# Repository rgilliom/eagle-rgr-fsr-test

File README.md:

# eagle-rgr-fsr-test
Ruger FSR Test Board for logging values using the 2-wire trigger circuit.  Eagle Project

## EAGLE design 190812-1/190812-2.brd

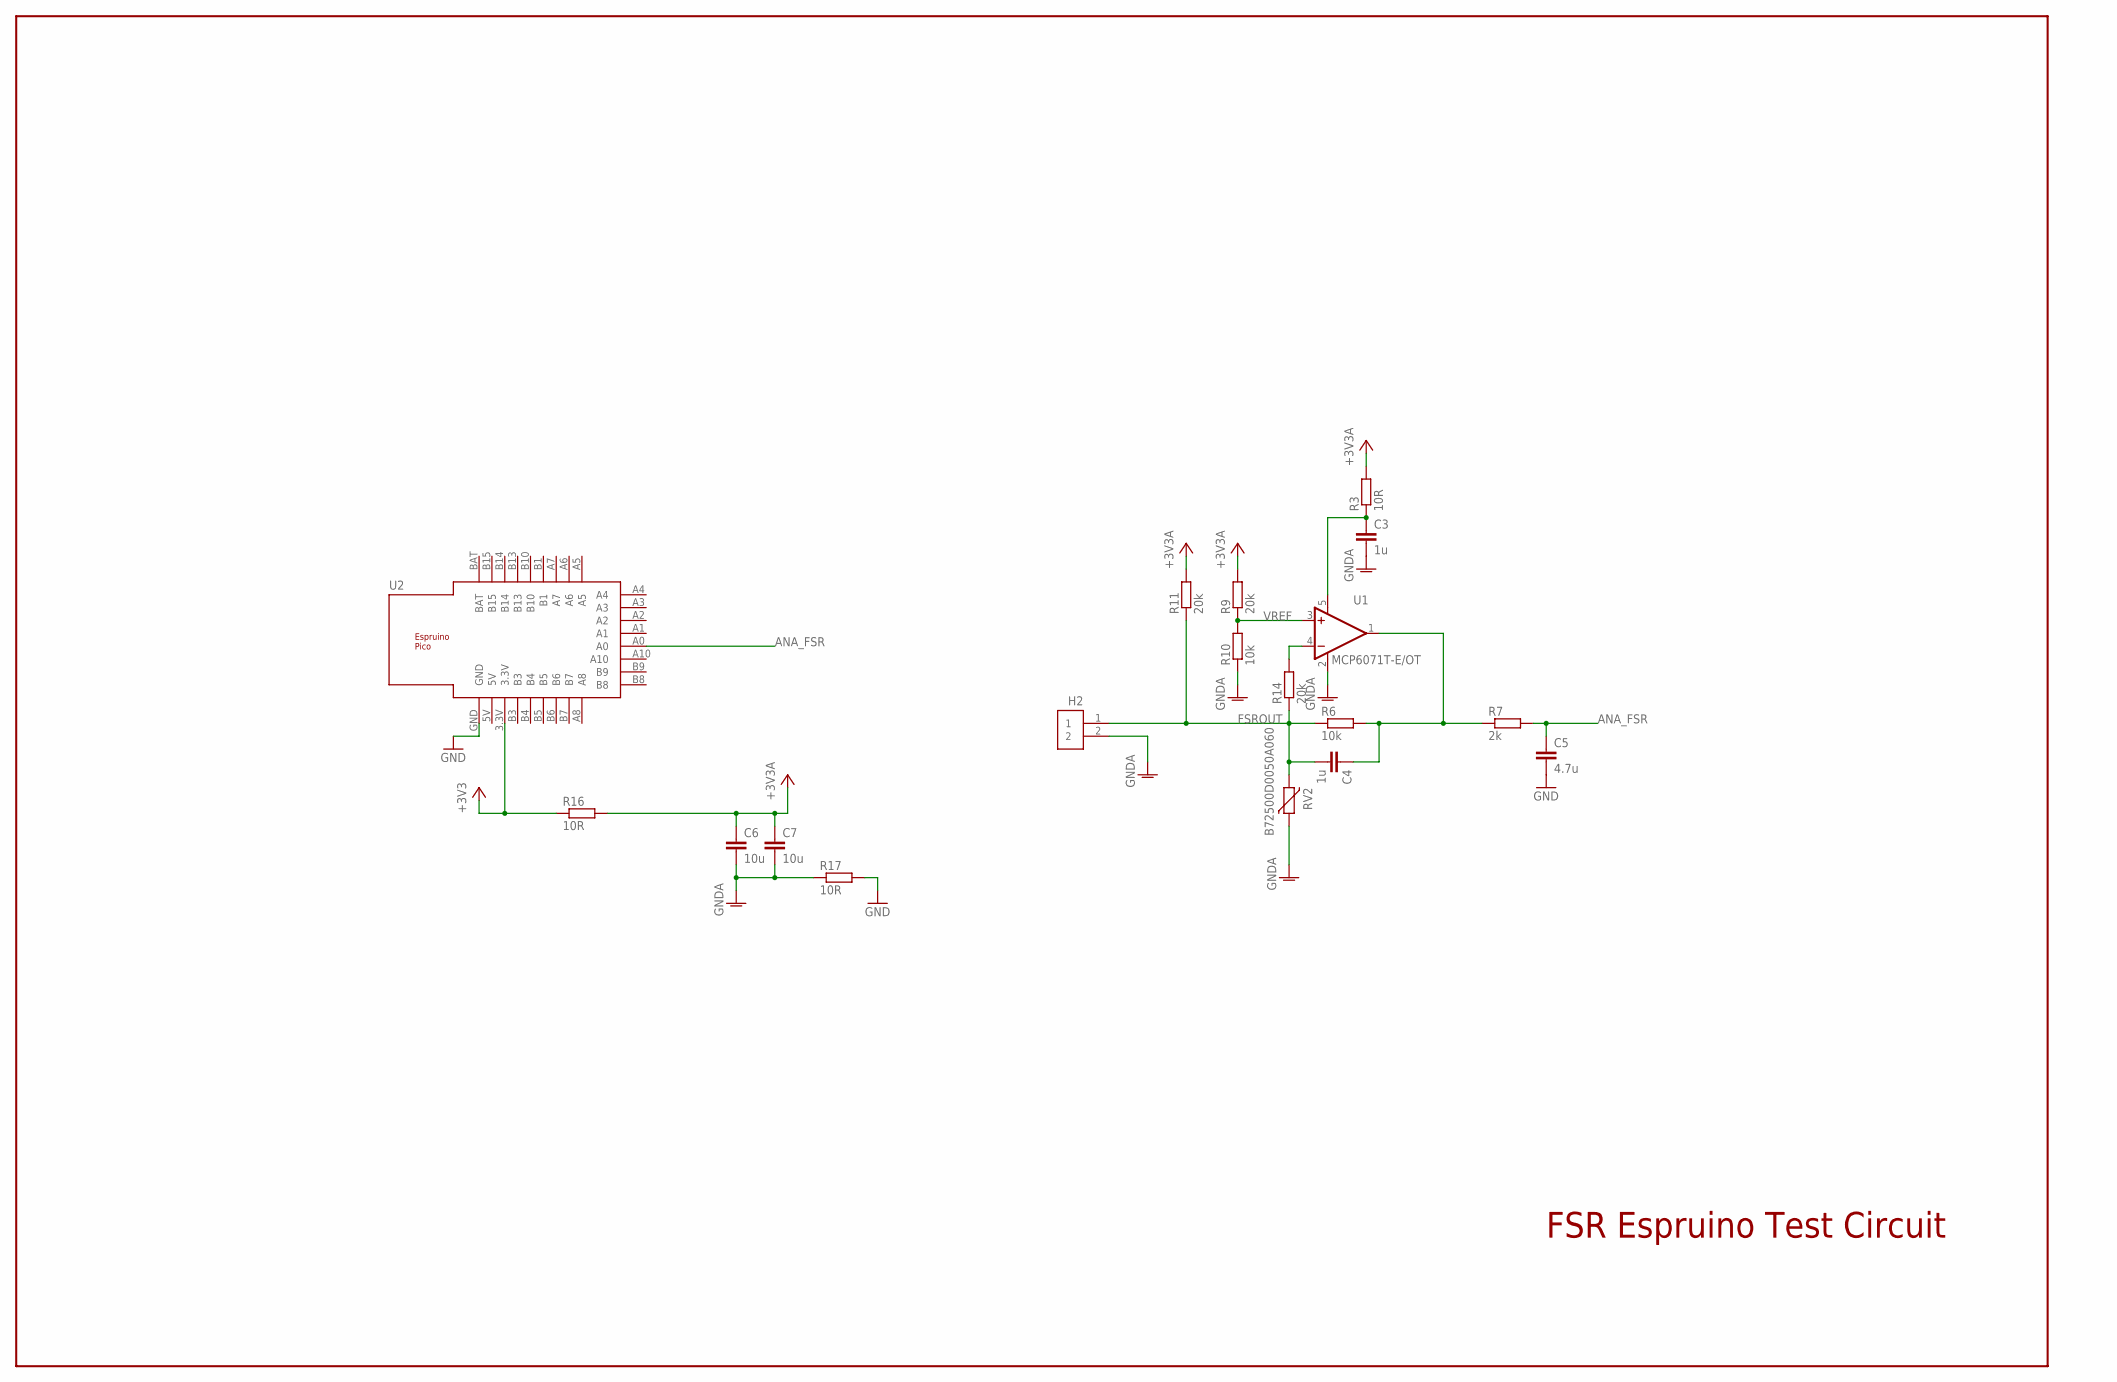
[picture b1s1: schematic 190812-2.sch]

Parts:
C3: 1u; C0603
C4: 1u; C0805
C5: 4.7u; C0805
C6, C7: 10u; C1206
H2: FSR-CONNECTOR-RUGER; 1X02
R3, R16, R17: 10R; R0603
R6, R10: 10k; R0603
R7: 2k; R0603
R9, R11, R14: 20k; R0603
RV2: B72500D0050A060; VARC1608X90
U1: MCP6071T-E/OT; SOT95P270X145-5
U2: ESPRUINO_PICO_SMDONLY

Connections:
+3V3: R16.1, U2.3.3V
+3V3A: C6.1, C7.1, R3.2, R9.2, R11.2, R16.2
ANA_FSR: C5.1, R7.2, U2.A0
FSROUT: C4.2, H2.1, R6.1, R11.1, R14.1, RV2.2
FSR_OUT2: C4.1, R6.2, R7.1, U1.1 (OUT)
GND: C5.2, R17.2, U2.GND
GNDA: C3.2, C6.2, C7.2, H2.2, R10.1, R17.1, RV2.1, U1.2 (V-)
unnamed: C3.1, R3.1, U1.5 (V+)
unnamed: R14.2, U1.4 (-IN)
VREF: R9.1, R10.2, U1.3 (+IN)

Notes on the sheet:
FSR Espruino Test Circuit

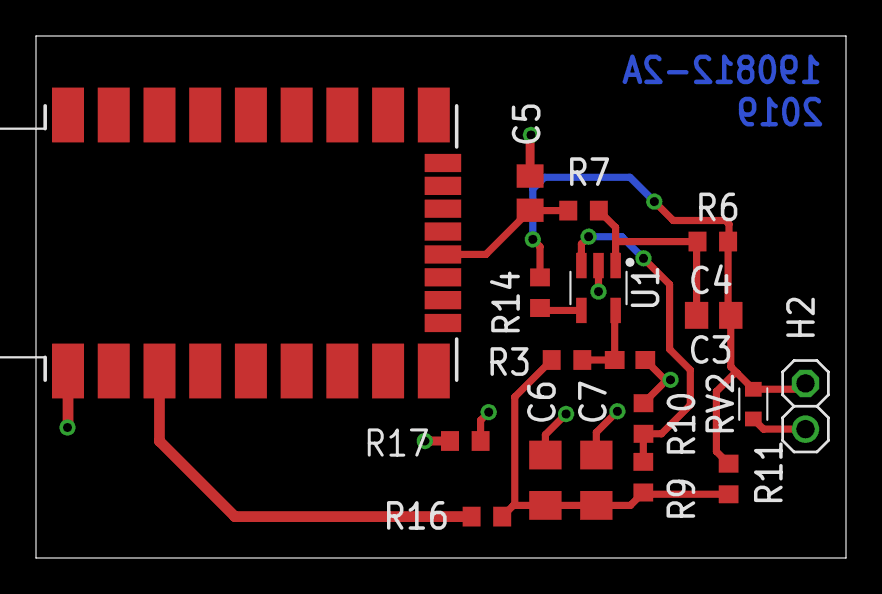
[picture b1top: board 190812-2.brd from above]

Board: 2 copper layers, 45.0 x 29.0 mm, 18 parts (0 on the bottom side), 10 nets.

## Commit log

2019-08-12 first pass design
2019-08-12 Boards were ordered from the commit. Sunstone circuits.
2019-08-15 Fixed schematic corruption. Reran CAM.
2019-08-21 added espruino code. WARNING eagle was corrupted double check.
